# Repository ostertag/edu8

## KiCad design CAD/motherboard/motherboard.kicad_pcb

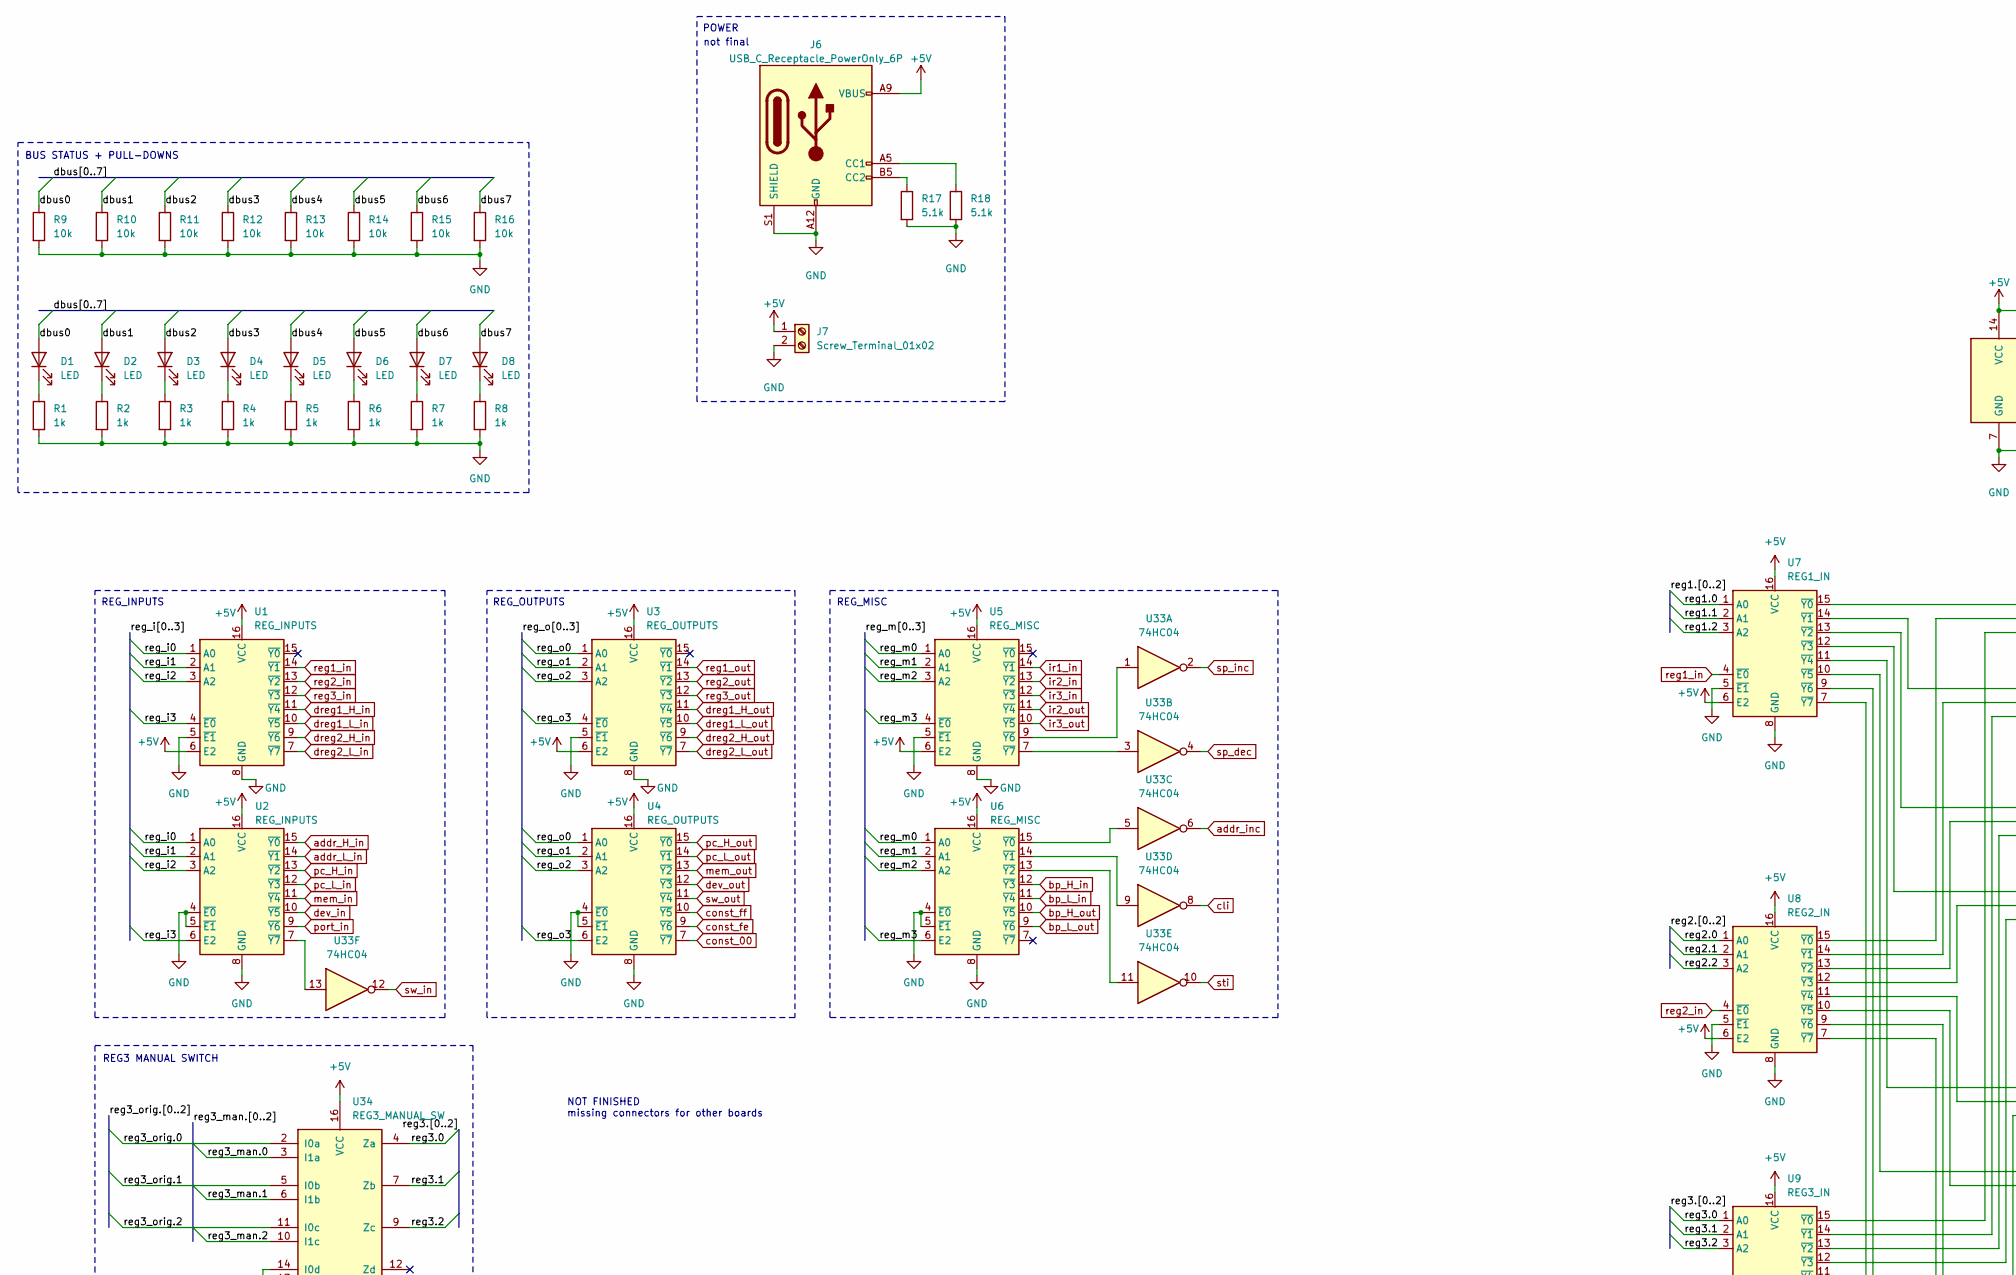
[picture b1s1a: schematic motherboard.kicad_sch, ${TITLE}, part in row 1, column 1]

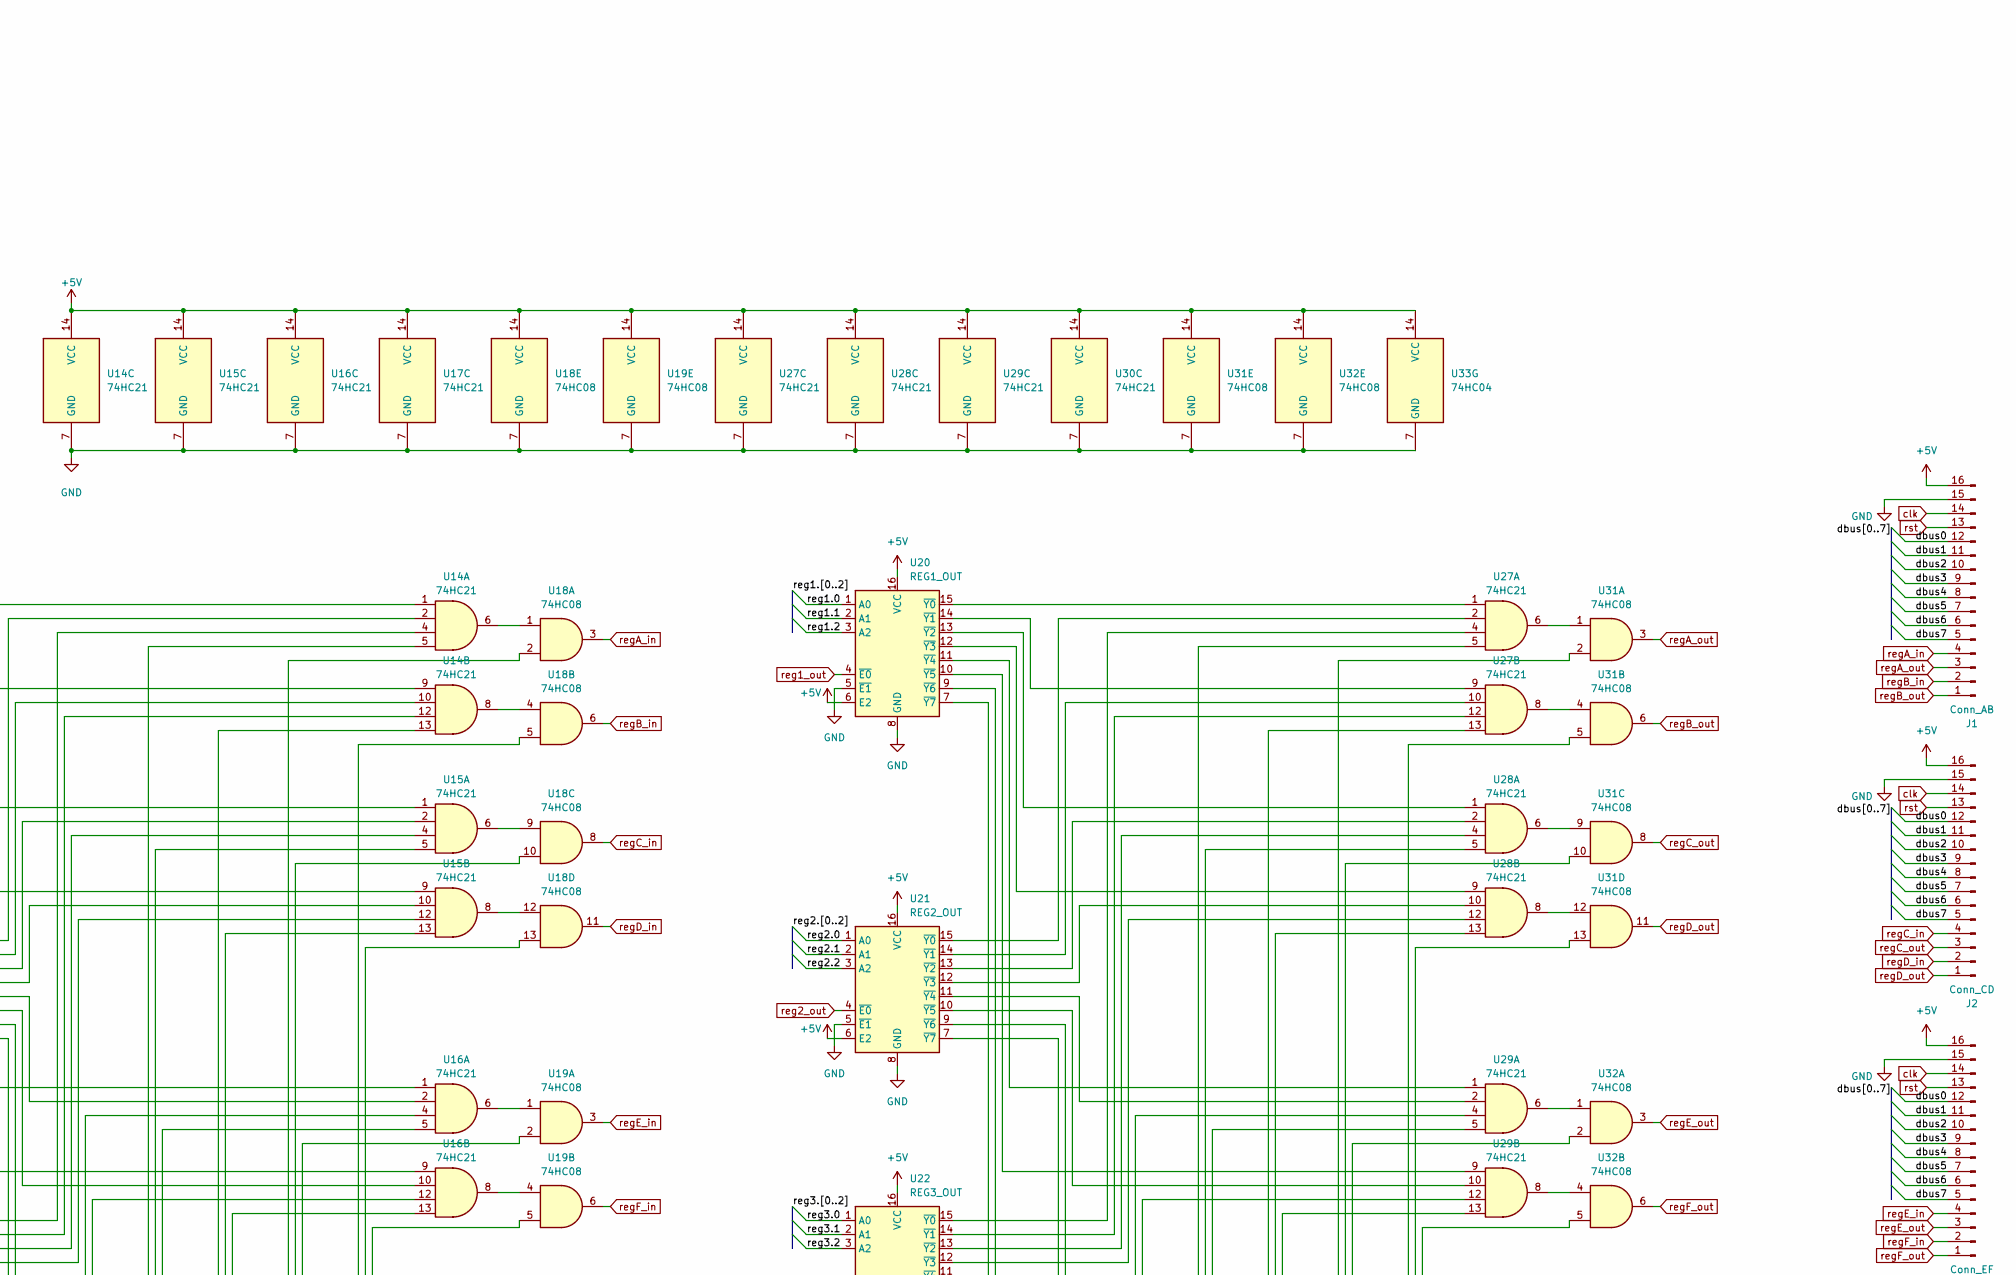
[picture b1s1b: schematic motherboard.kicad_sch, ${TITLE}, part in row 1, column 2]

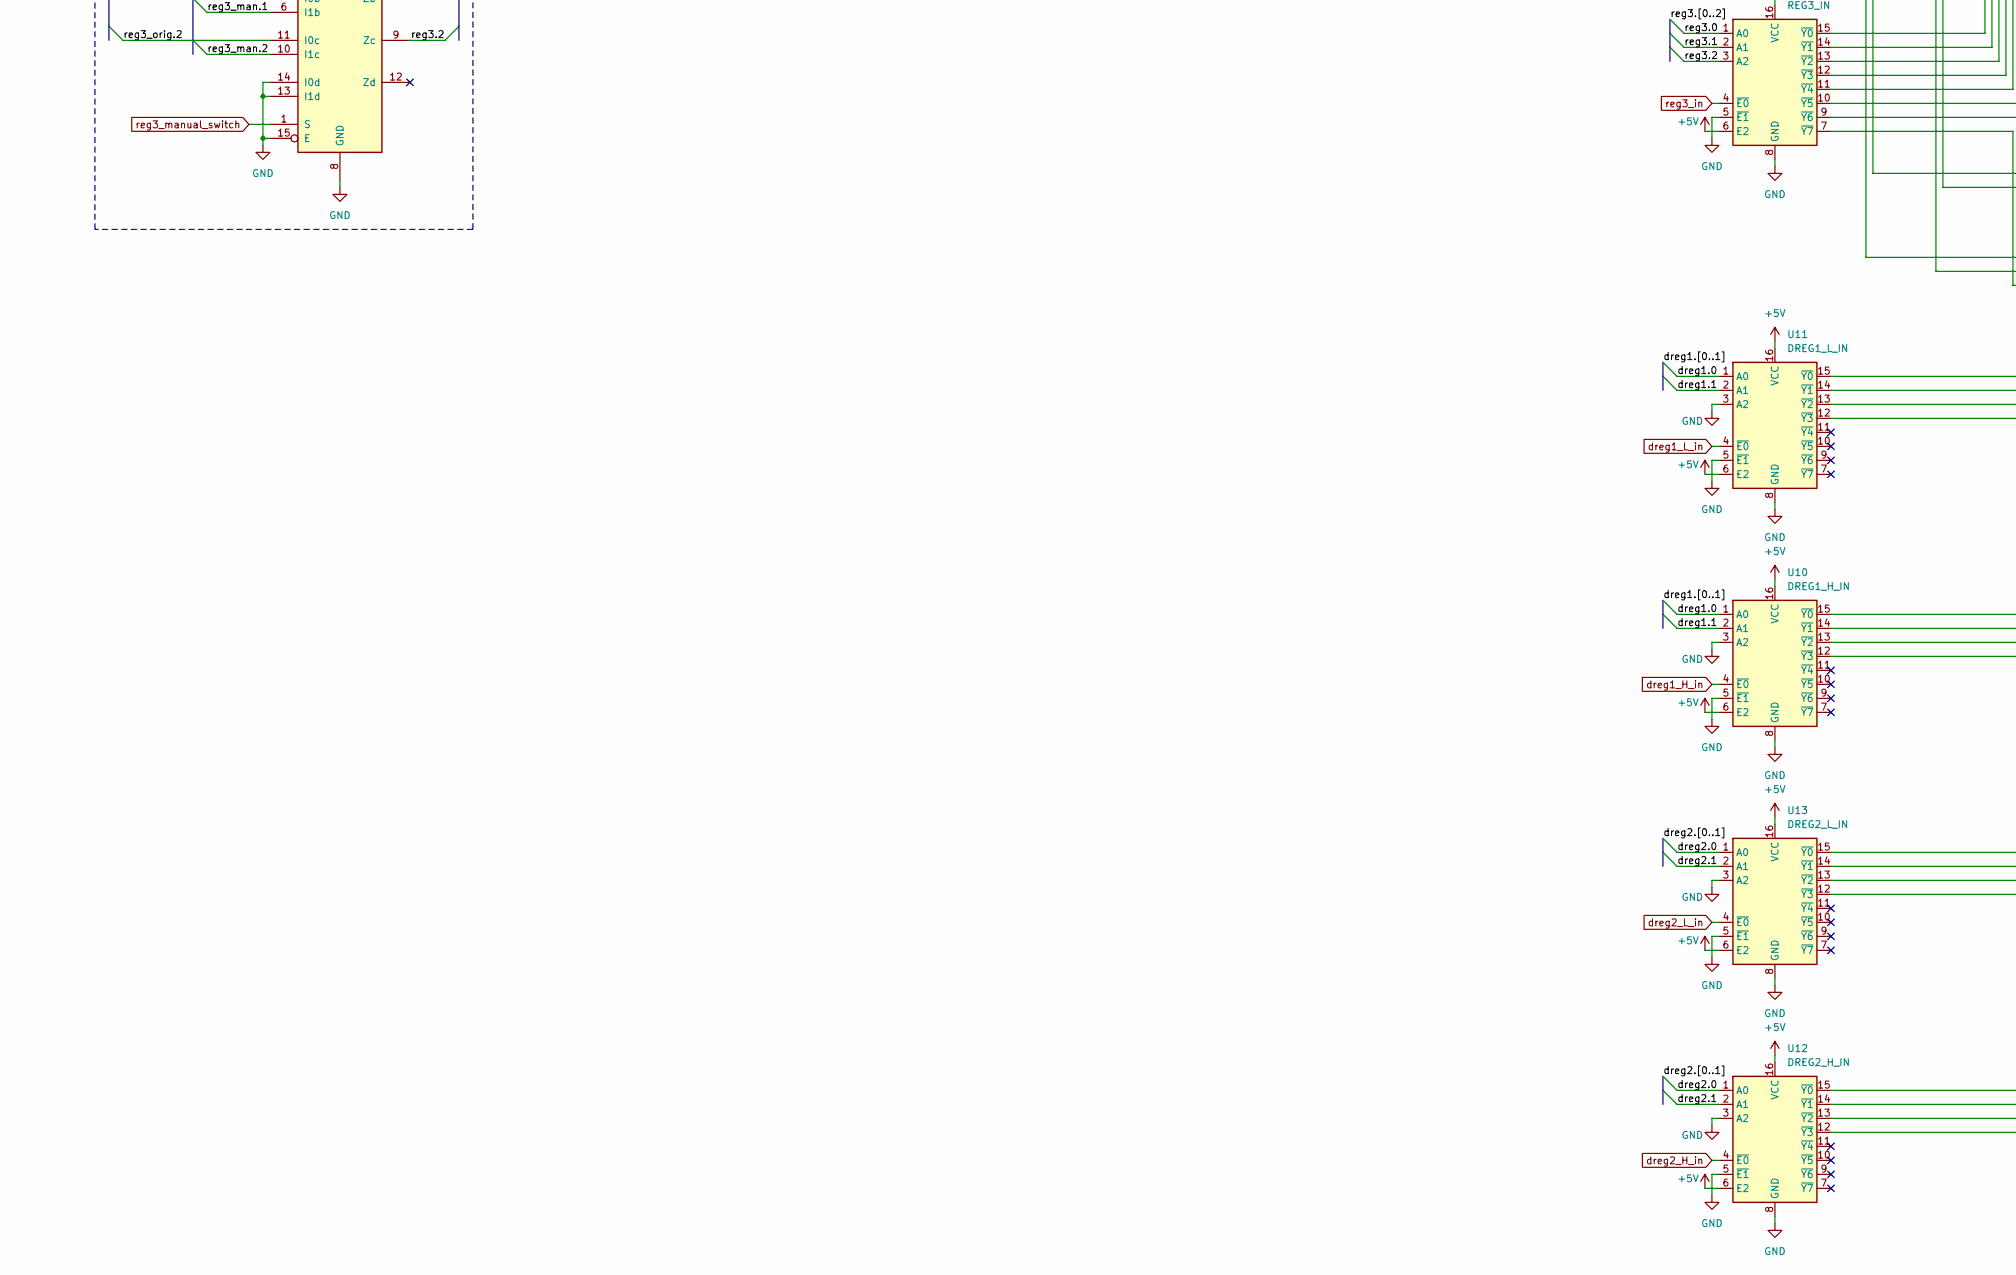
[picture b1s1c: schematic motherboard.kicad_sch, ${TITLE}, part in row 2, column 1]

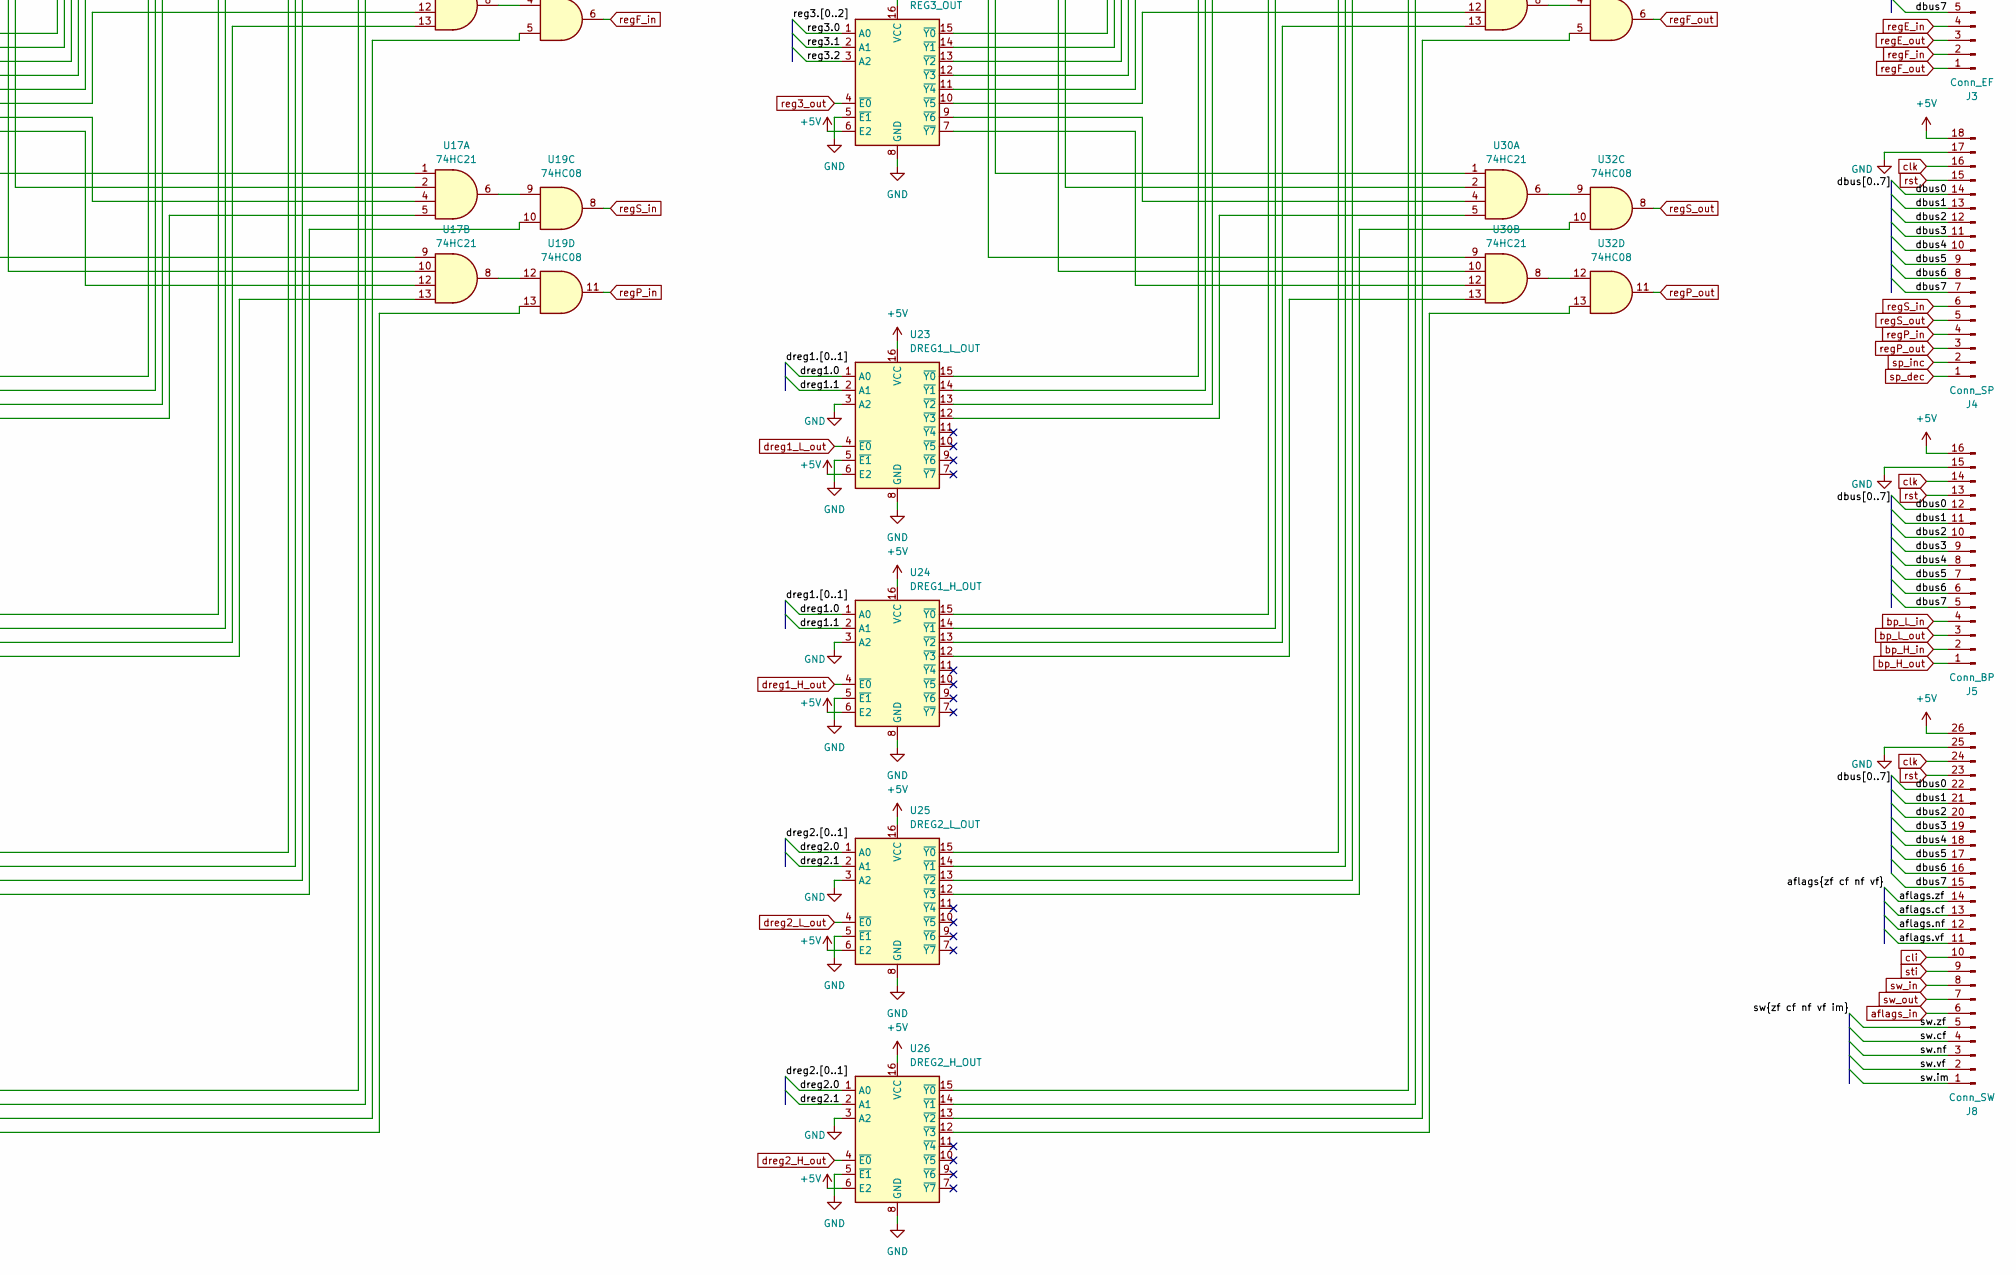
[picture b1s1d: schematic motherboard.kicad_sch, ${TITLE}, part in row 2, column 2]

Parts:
D1, D2, D3, D4, D5, D6, D7, D8: LED; LED_0805_2012Metric
J1: Conn_AB; PinSocket_2x08_P2.54mm_Horizontal
J2: Conn_CD; PinSocket_2x08_P2.54mm_Horizontal
J3: Conn_EF; PinSocket_2x08_P2.54mm_Horizontal
J4: Conn_SP; PinSocket_2x09_P2.54mm_Horizontal
J5: Conn_BP; PinSocket_2x08_P2.54mm_Horizontal
J6: USB_C_Receptacle_PowerOnly_6P; USB_C_Receptacle_GCT_USB4125-xx-x-0190_6P_TopMnt_Horizontal
J7: Screw_Terminal_01x02; TerminalBlock_4Ucon_1x02_P3.50mm_Horizontal
J8: Conn_SW; PinSocket_2x13_P2.54mm_Horizontal
R1, R2, R3, R4, R5, R6, R7, R8: 1k; R_0805_2012Metric
R9, R10, R11, R12, R13, R14, R15, R16: 10k; R_0805_2012Metric
R17, R18: 5.1k; R_0805_2012Metric
U1, U2: REG_INPUTS; SO-16_3.9x9.9mm_P1.27mm
U3, U4: REG_OUTPUTS; SO-16_3.9x9.9mm_P1.27mm
U5, U6: REG_MISC; SO-16_3.9x9.9mm_P1.27mm
U7: REG1_IN; SO-16_3.9x9.9mm_P1.27mm
U8: REG2_IN; SO-16_3.9x9.9mm_P1.27mm
U9: REG3_IN; SO-16_3.9x9.9mm_P1.27mm
U10: DREG1_H_IN; SO-16_3.9x9.9mm_P1.27mm
U11: DREG1_L_IN; SO-16_3.9x9.9mm_P1.27mm
U12: DREG2_H_IN; SO-16_3.9x9.9mm_P1.27mm
U13: DREG2_L_IN; SO-16_3.9x9.9mm_P1.27mm
U14, U15, U16, U17, U27, U28, U29, U30: 74HC21; SO-14_3.9x8.65mm_P1.27mm
U18, U19, U31, U32: 74HC08; SO-14_3.9x8.65mm_P1.27mm
U20: REG1_OUT; SO-16_3.9x9.9mm_P1.27mm
U21: REG2_OUT; SO-16_3.9x9.9mm_P1.27mm
U22: REG3_OUT; SO-16_3.9x9.9mm_P1.27mm
U23: DREG1_L_OUT; SO-16_3.9x9.9mm_P1.27mm
U24: DREG1_H_OUT; SO-16_3.9x9.9mm_P1.27mm
U25: DREG2_L_OUT; SO-16_3.9x9.9mm_P1.27mm
U26: DREG2_H_OUT; SO-16_3.9x9.9mm_P1.27mm
U33: 74HC04; SO-14_3.9x8.65mm_P1.27mm
U34: REG3_MANUAL_SW; SO-16_3.9x9.9mm_P1.27mm

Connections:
+5V: J1.16, J2.16, J3.16, J4.18, J5.16, J6.A9 (VBUS), J6.B9 (VBUS), J7.1, J8.26, U1.6 (E2), U1.16 (VCC), U2.16 (VCC), U3.6 (E2), U3.16 (VCC), U4.16 (VCC), U5.6 (E2), U5.16 (VCC), U6.16 (VCC), U7.6 (E2), U7.16 (VCC), U8.6 (E2), U8.16 (VCC), U9.6 (E2), U9.16 (VCC), U10.6 (E2), U10.16 (VCC), U11.6 (E2), U11.16 (VCC), U12.6 (E2), U12.16 (VCC), U13.6 (E2), U13.16 (VCC), U14.14 (VCC), U15.14 (VCC), U16.14 (VCC), U17.14 (VCC), U18.14 (VCC), U19.14 (VCC), U20.6 (E2), U20.16 (VCC), U21.6 (E2), U21.16 (VCC), U22.6 (E2), U22.16 (VCC), U23.6 (E2), U23.16 (VCC), U24.6 (E2), U24.16 (VCC), U25.6 (E2), U25.16 (VCC), U26.6 (E2), U26.16 (VCC), U27.14 (VCC), U28.14 (VCC), U29.14 (VCC), U30.14 (VCC), U31.14 (VCC), U32.14 (VCC), U33.14 (VCC), U34.16 (VCC)
/aflags.cf: J8.13
/aflags.nf: J8.12
/aflags.vf: J8.11
/aflags.zf: J8.14
/dbus0: D1.2 (A), J1.12, J2.12, J3.12, J4.14, J5.12, J8.22, R9.1
/dbus1: D2.2 (A), J1.11, J2.11, J3.11, J4.13, J5.11, J8.21, R10.1
/dbus2: D3.2 (A), J1.10, J2.10, J3.10, J4.12, J5.10, J8.20, R11.1
/dbus3: D4.2 (A), J1.9, J2.9, J3.9, J4.11, J5.9, J8.19, R12.1
/dbus4: D5.2 (A), J1.8, J2.8, J3.8, J4.10, J5.8, J8.18, R13.1
/dbus5: D6.2 (A), J1.7, J2.7, J3.7, J4.9, J5.7, J8.17, R14.1
/dbus6: D7.2 (A), J1.6, J2.6, J3.6, J4.8, J5.6, J8.16, R15.1
/dbus7: D8.2 (A), J1.5, J2.5, J3.5, J4.7, J5.5, J8.15, R16.1
/dreg1.0: U10.1 (A0), U11.1 (A0), U23.1 (A0), U24.1 (A0)
/dreg1.1: U10.2 (A1), U11.2 (A1), U23.2 (A1), U24.2 (A1)
/dreg2.0: U12.1 (A0), U13.1 (A0), U25.1 (A0), U26.1 (A0)
/dreg2.1: U12.2 (A1), U13.2 (A1), U25.2 (A1), U26.2 (A1)
/reg1.0: U7.1 (A0), U20.1 (A0)
/reg1.1: U7.2 (A1), U20.2 (A1)
/reg1.2: U7.3 (A2), U20.3 (A2)
/reg2.0: U8.1 (A0), U21.1 (A0)
/reg2.1: U8.2 (A1), U21.2 (A1)
/reg2.2: U8.3 (A2), U21.3 (A2)
/reg3.0: U9.1 (A0), U22.1 (A0), U34.4 (Za)
/reg3.1: U9.2 (A1), U22.2 (A1), U34.7 (Zb)
/reg3.2: U9.3 (A2), U22.3 (A2), U34.9 (Zc)
/reg3_man.0: U34.3 (I1a)
/reg3_man.1: U34.6 (I1b)
/reg3_man.2: U34.10 (I1c)
/reg3_orig.0: U34.2 (I0a)
/reg3_orig.1: U34.5 (I0b)
/reg3_orig.2: U34.11 (I0c)
/reg_i0: U1.1 (A0), U2.1 (A0)
/reg_i1: U1.2 (A1), U2.2 (A1)
/reg_i2: U1.3 (A2), U2.3 (A2)
/reg_i3: U1.4 (~E0), U2.6 (E2)
/reg_m0: U5.1 (A0), U6.1 (A0)
/reg_m1: U5.2 (A1), U6.2 (A1)
/reg_m2: U5.3 (A2), U6.3 (A2)
/reg_m3: U5.4 (~E0), U6.6 (E2)
/reg_o0: U3.1 (A0), U4.1 (A0)
/reg_o1: U3.2 (A1), U4.2 (A1)
/reg_o2: U3.3 (A2), U4.3 (A2)
/reg_o3: U3.4 (~E0), U4.6 (E2)
/sw.cf: J8.4
/sw.im: J8.1
/sw.nf: J8.3
/sw.vf: J8.2
/sw.zf: J8.5
GND: J1.15, J2.15, J3.15, J4.17, J5.15, J6.A12 (GND), J6.B12 (GND), J6.S1 (SHIELD), J7.2, J8.25, R1.2, R2.2, R3.2, R4.2, R5.2, R6.2, R7.2, R8.2, R9.2, R10.2, R11.2, R12.2, R13.2, R14.2, R15.2, R16.2, R17.2, R18.2, U1.5 (~E1), U1.8 (GND), U2.4 (~E0), U2.5 (~E1), U2.8 (GND), U3.5 (~E1), U3.8 (GND), U4.4 (~E0), U4.5 (~E1), U4.8 (GND), U5.5 (~E1), U5.8 (GND), U6.4 (~E0), U6.5 (~E1), U6.8 (GND), U7.5 (~E1), U7.8 (GND), U8.5 (~E1), U8.8 (GND), U9.5 (~E1), U9.8 (GND), U10.3 (A2), U10.5 (~E1), U10.8 (GND), U11.3 (A2), U11.5 (~E1), U11.8 (GND), U12.3 (A2), U12.5 (~E1), U12.8 (GND), U13.3 (A2), U13.5 (~E1), U13.8 (GND), U14.7 (GND), U15.7 (GND), U16.7 (GND), U17.7 (GND), U18.7 (GND), U19.7 (GND), U20.5 (~E1), U20.8 (GND), U21.5 (~E1), U21.8 (GND), U22.5 (~E1), U22.8 (GND), U23.3 (A2), U23.5 (~E1), U23.8 (GND), U24.3 (A2), U24.5 (~E1), U24.8 (GND), U25.3 (A2), U25.5 (~E1), U25.8 (GND), U26.3 (A2), U26.5 (~E1), U26.8 (GND), U27.7 (GND), U28.7 (GND), U29.7 (GND), U30.7 (GND), U31.7 (GND), U32.7 (GND), U33.7 (GND), U34.8 (GND), U34.13 (I1d), U34.14 (I0d), U34.15 (E)
unnamed: D1.1 (K), R1.1
unnamed: D2.1 (K), R2.1
unnamed: D3.1 (K), R3.1
unnamed: D4.1 (K), R4.1
unnamed: D5.1 (K), R5.1
unnamed: D6.1 (K), R6.1
unnamed: D7.1 (K), R7.1
unnamed: D8.1 (K), R8.1
unnamed: J6.A5 (CC1), R18.1
unnamed: J6.B5 (CC2), R17.1
unnamed: U2.7 (~Y7), U33.13
unnamed: U5.9 (~Y6), U33.1
unnamed: U5.7 (~Y7), U33.3
unnamed: U6.15 (~Y0), U33.5
unnamed: U6.14 (~Y1), U33.9
unnamed: U6.13 (~Y2), U33.11
unnamed: U7.15 (~Y0), U14.1
unnamed: U7.14 (~Y1), U14.9
unnamed: U7.13 (~Y2), U15.1
unnamed: U7.12 (~Y3), U15.9
unnamed: U7.11 (~Y4), U16.1
unnamed: U7.10 (~Y5), U16.9
unnamed: U7.9 (~Y6), U17.1
unnamed: U7.7 (~Y7), U17.9
unnamed: U8.15 (~Y0), U14.2
unnamed: U8.14 (~Y1), U14.10
unnamed: U8.13 (~Y2), U15.2
unnamed: U8.12 (~Y3), U15.10
unnamed: U8.11 (~Y4), U16.2
unnamed: U8.10 (~Y5), U16.10
unnamed: U8.9 (~Y6), U17.2
unnamed: U8.7 (~Y7), U17.10
unnamed: U9.15 (~Y0), U14.4
unnamed: U9.14 (~Y1), U14.12
unnamed: U9.13 (~Y2), U15.4
unnamed: U9.12 (~Y3), U15.12
unnamed: U9.11 (~Y4), U16.4
unnamed: U9.10 (~Y5), U16.12
unnamed: U9.9 (~Y6), U17.4
unnamed: U9.7 (~Y7), U17.12
unnamed: U10.15 (~Y0), U14.13
unnamed: U10.14 (~Y1), U15.13
unnamed: U10.13 (~Y2), U16.13
unnamed: U10.12 (~Y3), U17.13
unnamed: U11.15 (~Y0), U14.5
unnamed: U11.14 (~Y1), U15.5
unnamed: U11.13 (~Y2), U16.5
unnamed: U11.12 (~Y3), U17.5
unnamed: U12.15 (~Y0), U18.5
unnamed: U12.14 (~Y1), U18.13
unnamed: U12.13 (~Y2), U19.5
unnamed: U12.12 (~Y3), U19.13
unnamed: U13.15 (~Y0), U18.2
unnamed: U13.14 (~Y1), U18.10
unnamed: U13.13 (~Y2), U19.2
unnamed: U13.12 (~Y3), U19.10
unnamed: U14.6, U18.1
unnamed: U14.8, U18.4
unnamed: U15.6, U18.9
unnamed: U15.8, U18.12
unnamed: U16.6, U19.1
unnamed: U16.8, U19.4
unnamed: U17.6, U19.9
unnamed: U17.8, U19.12
unnamed: U20.15 (~Y0), U27.1
unnamed: U20.14 (~Y1), U27.9
unnamed: U20.13 (~Y2), U28.1
unnamed: U20.12 (~Y3), U28.9
unnamed: U20.11 (~Y4), U29.1
unnamed: U20.10 (~Y5), U29.9
unnamed: U20.9 (~Y6), U30.1
unnamed: U20.7 (~Y7), U30.9
unnamed: U21.15 (~Y0), U27.2
unnamed: U21.14 (~Y1), U27.10
unnamed: U21.13 (~Y2), U28.2
unnamed: U21.12 (~Y3), U28.10
unnamed: U21.11 (~Y4), U29.2
unnamed: U21.10 (~Y5), U29.10
unnamed: U21.9 (~Y6), U30.2
unnamed: U21.7 (~Y7), U30.10
unnamed: U22.15 (~Y0), U27.4
unnamed: U22.14 (~Y1), U27.12
unnamed: U22.13 (~Y2), U28.4
unnamed: U22.12 (~Y3), U28.12
unnamed: U22.11 (~Y4), U29.4
unnamed: U22.10 (~Y5), U29.12
unnamed: U22.9 (~Y6), U30.4
unnamed: U22.7 (~Y7), U30.12
unnamed: U23.15 (~Y0), U27.5
unnamed: U23.14 (~Y1), U28.5
unnamed: U23.13 (~Y2), U29.5
unnamed: U23.12 (~Y3), U30.5
unnamed: U24.15 (~Y0), U27.13
unnamed: U24.14 (~Y1), U28.13
unnamed: U24.13 (~Y2), U29.13
unnamed: U24.12 (~Y3), U30.13
unnamed: U25.15 (~Y0), U31.2
unnamed: U25.14 (~Y1), U31.10
unnamed: U25.13 (~Y2), U32.2
unnamed: U25.12 (~Y3), U32.10
unnamed: U26.15 (~Y0), U31.5
unnamed: U26.14 (~Y1), U31.13
unnamed: U26.13 (~Y2), U32.5
unnamed: U26.12 (~Y3), U32.13
unnamed: U27.6, U31.1
unnamed: U27.8, U31.4
unnamed: U28.6, U31.9
unnamed: U28.8, U31.12
unnamed: U29.6, U32.1
unnamed: U29.8, U32.4
unnamed: U30.6, U32.9
unnamed: U30.8, U32.12
addr_H_in: U2.15 (~Y0)
addr_L_in: U2.14 (~Y1)
addr_inc: U33.6
aflags_in: J8.6
bp_H_in: J5.2, U6.12 (~Y3)
bp_H_out: J5.1, U6.10 (~Y5)
bp_L_in: J5.4, U6.11 (~Y4)
bp_L_out: J5.3, U6.9 (~Y6)
cli: J8.10, U33.8
clk: J1.14, J2.14, J3.14, J4.16, J5.14, J8.24
const_00: U4.7 (~Y7)
const_fe: U4.9 (~Y6)
const_ff: U4.10 (~Y5)
dev_in: U2.10 (~Y5)
dev_out: U4.12 (~Y3)
dreg1_H_in: U1.11 (~Y4), U10.4 (~E0)
dreg1_H_out: U3.11 (~Y4), U24.4 (~E0)
dreg1_L_in: U1.10 (~Y5), U11.4 (~E0)
dreg1_L_out: U3.10 (~Y5), U23.4 (~E0)
dreg2_H_in: U1.9 (~Y6), U12.4 (~E0)
dreg2_H_out: U3.9 (~Y6), U26.4 (~E0)
dreg2_L_in: U1.7 (~Y7), U13.4 (~E0)
dreg2_L_out: U3.7 (~Y7), U25.4 (~E0)
ir1_in: U5.14 (~Y1)
ir2_in: U5.13 (~Y2)
ir2_out: U5.11 (~Y4)
ir3_in: U5.12 (~Y3)
ir3_out: U5.10 (~Y5)
mem_in: U2.11 (~Y4)
mem_out: U4.13 (~Y2)
pc_H_in: U2.13 (~Y2)
pc_H_out: U4.15 (~Y0)
pc_L_in: U2.12 (~Y3)
pc_L_out: U4.14 (~Y1)
port_in: U2.9 (~Y6)
reg1_in: U1.14 (~Y1), U7.4 (~E0)
reg1_out: U3.14 (~Y1), U20.4 (~E0)
reg2_in: U1.13 (~Y2), U8.4 (~E0)
reg2_out: U3.13 (~Y2), U21.4 (~E0)
reg3_in: U1.12 (~Y3), U9.4 (~E0)
reg3_manual_switch: U34.1 (S)
reg3_out: U3.12 (~Y3), U22.4 (~E0)
regA_in: J1.4, U18.3
regA_out: J1.3, U31.3
regB_in: J1.2, U18.6
regB_out: J1.1, U31.6
regC_in: J2.4, U18.8
regC_out: J2.3, U31.8
regD_in: J2.2, U18.11
regD_out: J2.1, U31.11
regE_in: J3.4, U19.3
regE_out: J3.3, U32.3
regF_in: J3.2, U19.6
regF_out: J3.1, U32.6
regP_in: J4.4, U19.11
regP_out: J4.3, U32.11
regS_in: J4.6, U19.8
regS_out: J4.5, U32.8
rst: J1.13, J2.13, J3.13, J4.15, J5.13, J8.23
sp_dec: J4.1, U33.4
sp_inc: J4.2, U33.2
sti: J8.9, U33.10
sw_in: J8.8, U33.12
sw_out: J8.7, U4.11 (~Y4)

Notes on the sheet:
REG_INPUTS
REG_OUTPUTS
NOT FINISHED missing connectors for other boards
BUS STATUS + PULL-DOWNS
not final
POWER
REG3 MANUAL SWITCH
REG_MISC

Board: 2 copper layers, 68 parts (0 on the bottom side), 189 nets, no tracks yet.

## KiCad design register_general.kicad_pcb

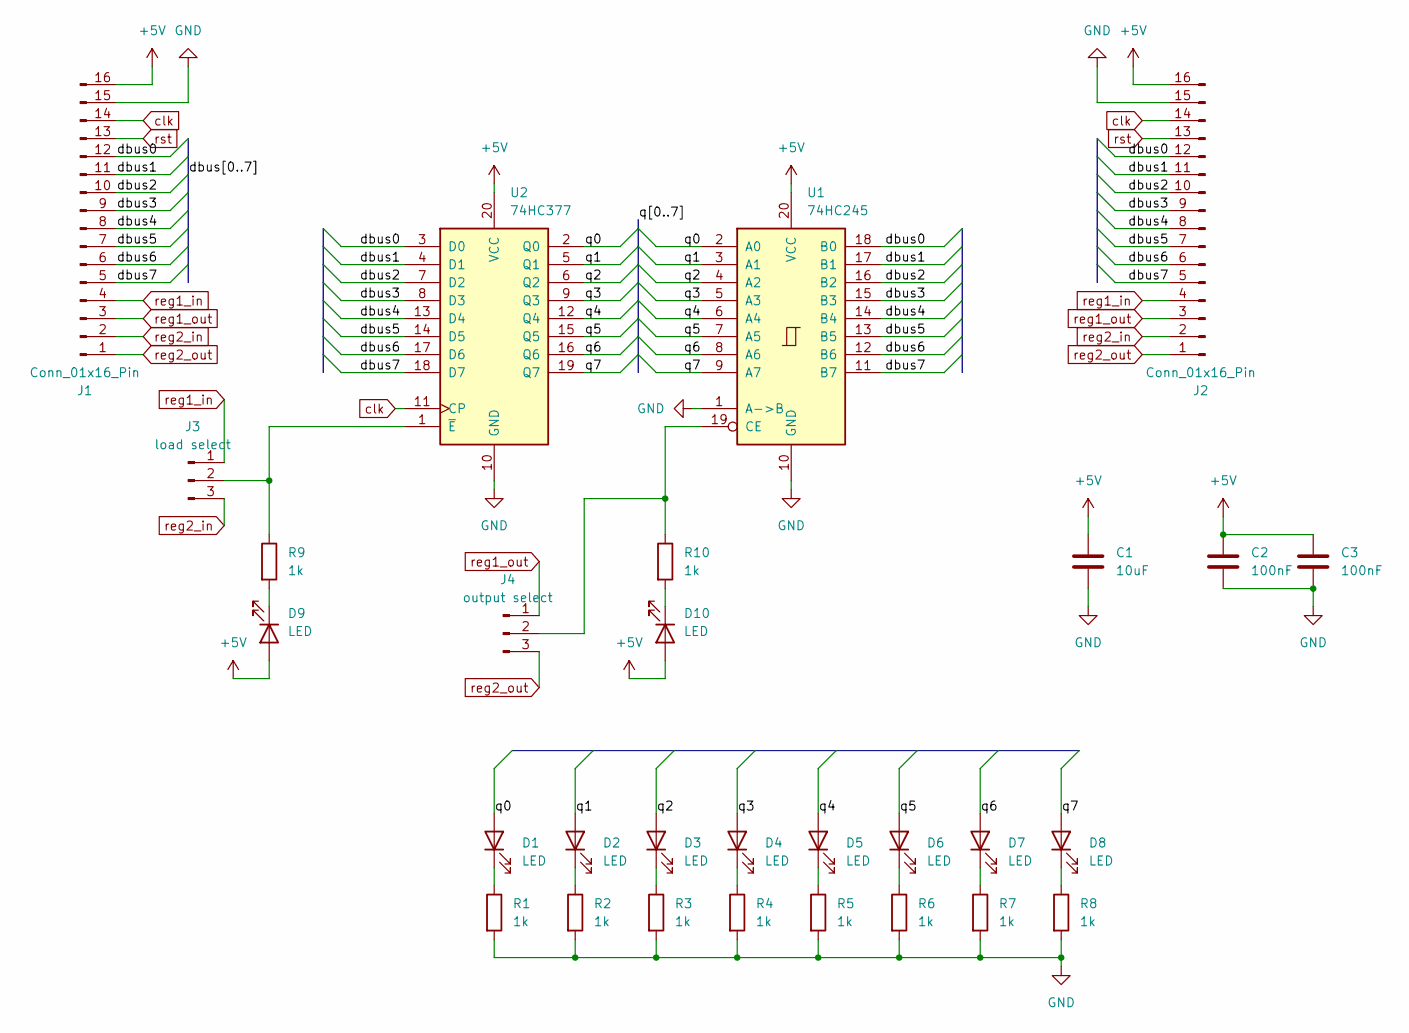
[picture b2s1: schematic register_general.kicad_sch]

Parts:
C1: 10uF; C_0805_2012Metric
C2, C3: 100nF; C_0805_2012Metric
D1, D2, D3, D4, D5, D6, D7, D8, D9, D10: LED; LED_0805_2012Metric
J1: Conn_01x16_Pin; PinHeader_2x08_P2.54mm_Horizontal
J2: Conn_01x16_Pin; PinSocket_2x08_P2.54mm_Horizontal
J3: load select; PinHeader_1x03_P2.54mm_Vertical
J4: output select; PinHeader_1x03_P2.54mm_Vertical
R1, R2, R3, R4, R5, R6, R7, R8, R9, R10: 1k; R_0805_2012Metric
U1: 74HC245; SO-20_5.3x12.6mm_P1.27mm
U2: 74HC377; SO-20_5.3x12.6mm_P1.27mm

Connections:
+5V: C1.1, C2.1, C3.1, D9.2 (A), D10.2 (A), J1.16, J2.16, U1.20 (VCC), U2.20 (VCC)
/dbus0: J1.12, J2.12, U1.18 (B0), U2.3 (D0)
/dbus1: J1.11, J2.11, U1.17 (B1), U2.4 (D1)
/dbus2: J1.10, J2.10, U1.16 (B2), U2.7 (D2)
/dbus3: J1.9, J2.9, U1.15 (B3), U2.8 (D3)
/dbus4: J1.8, J2.8, U1.14 (B4), U2.13 (D4)
/dbus5: J1.7, J2.7, U1.13 (B5), U2.14 (D5)
/dbus6: J1.6, J2.6, U1.12 (B6), U2.17 (D6)
/dbus7: J1.5, J2.5, U1.11 (B7), U2.18 (D7)
/q0: D1.2 (A), U1.2 (A0), U2.2 (Q0)
/q1: D2.2 (A), U1.3 (A1), U2.5 (Q1)
/q2: D3.2 (A), U1.4 (A2), U2.6 (Q2)
/q3: D4.2 (A), U1.5 (A3), U2.9 (Q3)
/q4: D5.2 (A), U1.6 (A4), U2.12 (Q4)
/q5: D6.2 (A), U1.7 (A5), U2.15 (Q5)
/q6: D7.2 (A), U1.8 (A6), U2.16 (Q6)
/q7: D8.2 (A), U1.9 (A7), U2.19 (Q7)
GND: C1.2, C2.2, C3.2, J1.15, J2.15, R1.2, R2.2, R3.2, R4.2, R5.2, R6.2, R7.2, R8.2, U1.1 (A->B), U1.10 (GND), U2.10 (GND)
unnamed: D1.1 (K), R1.1
unnamed: D2.1 (K), R2.1
unnamed: D3.1 (K), R3.1
unnamed: D4.1 (K), R4.1
unnamed: D5.1 (K), R5.1
unnamed: D6.1 (K), R6.1
unnamed: D7.1 (K), R7.1
unnamed: D8.1 (K), R8.1
unnamed: D9.1 (K), R9.2
unnamed: D10.1 (K), R10.2
unnamed: J3.2, R9.1, U2.1 (~E)
unnamed: J4.2, R10.1, U1.19 (CE)
clk: J1.14, J2.14, U2.11 (CP)
reg1_in: J1.4, J2.4, J3.1
reg1_out: J1.3, J2.3, J4.1
reg2_in: J1.2, J2.2, J3.3
reg2_out: J1.1, J2.1, J4.3
rst: J1.13, J2.13

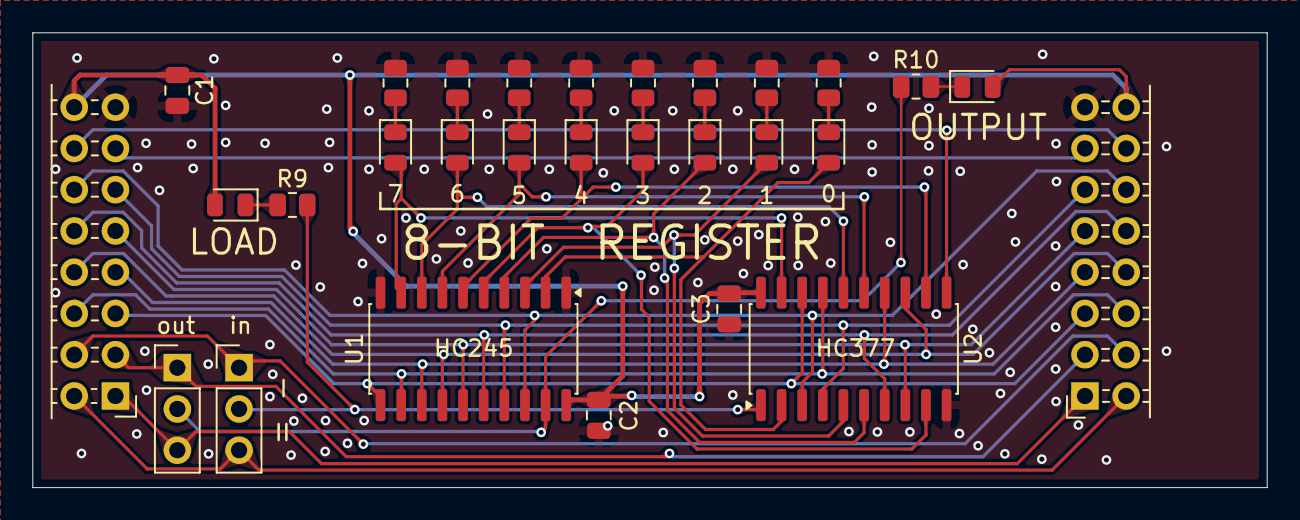
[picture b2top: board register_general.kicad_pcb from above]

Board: 4 copper layers, 76.0 x 28.0 mm, 29 parts (0 on the bottom side), 36 nets.
